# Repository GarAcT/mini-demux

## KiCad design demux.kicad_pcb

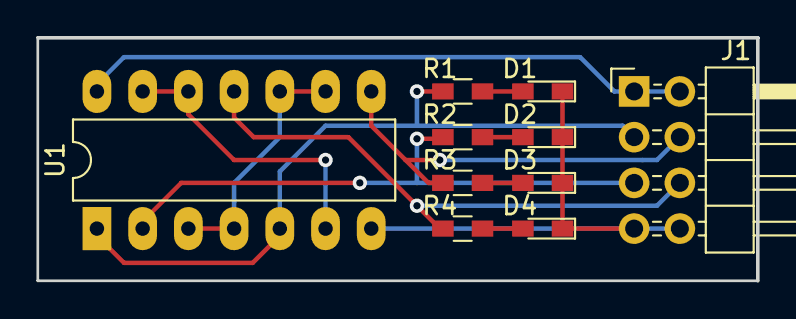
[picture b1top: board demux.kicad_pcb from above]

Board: 2 copper layers, 40.0 x 13.5 mm, 10 parts (0 on the bottom side), 12 nets.

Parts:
D1, D2, D3, D4: LED; LED_0603_HandSoldering
J1: Conn_02x04_Odd_Even; Pin_Header_Angled_2x04_Pitch2.54mm
R1, R2, R3, R4: R; R_0603_HandSoldering
U1: 74LS00; DIP-14_W7.62mm_LongPads

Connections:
/In: J1.3, R1.1, U1.1, U1.5
/Out1: J1.4, R3.1, U1.8
/Out2: J1.6, R4.1, U1.11
/Sel: J1.5, R2.1, U1.2
GND: D1.1, D2.1, D3.1, D4.1, J1.7, J1.8, U1.7
unnamed: D1.2, R1.2
unnamed: D2.2, R2.2
unnamed: D3.2, R3.2
unnamed: D4.2, R4.2
unnamed: U1.3, U1.4, U1.9, U1.10
unnamed: U1.6, U1.12, U1.13
VCC: J1.1, J1.2, U1.14
